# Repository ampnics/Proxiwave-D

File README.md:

# ProxiWave-D (PWD-v010A)
### Touchless Proximity-Based AC Relay Controller — Open Source Hardware by Ampnics

> An open-source, touchless proximity-based AC relay controller built on ATmega328-A with a VL53L0X Time-of-Flight sensor — designed for contactless switching of 220VAC loads by detecting hand proximity within 10–30mm range.

---

## 📸 Board Preview

| PCB Top View (Sensor Side) | PCB Bottom View (Power Side) |

---

---

## 📋 Table of Contents

- [Overview](#-overview)
- [Features](#-features)
- [How It Works](#-how-it-works)
- [Hardware Specifications](#-hardware-specifications)
- [GPIO Mapping](#-gpio-mapping)
- [Pin Description](#-pin-description)
- [Repository Structure](#-repository-structure)
- [Getting Started](#-getting-started)
- [Firmware Setup](#-firmware-setup)
- [Calibration](#-calibration)
- [Manufacturing](#-manufacturing)
- [Safety Warning](#️-safety-warning)
- [Contributing](#-contributing)
- [Support Us](#-support-us)
- [Connect With Us](#-connect-with-us)
- [License](#-license)

---

## 🔍 Overview

The **ProxiWave-D** is an open-source, touchless proximity relay controller designed for contactless switching of 220VAC loads. It uses a **VL53L0X Time-of-Flight (ToF) distance sensor** to detect hand proximity within a calibrated range of **10mm to 30mm**, triggering an onboard relay to switch AC loads — no physical contact required.

The board runs on **220VAC mains input**, converting it to **5V DC** via an onboard HLK-5M05 power supply module, and further to **3.3V** via an AMS1117-3.3 LDO — powering the ATmega328 and the VL53L0X sensor.

A **backup IR sensor connector (J3)** is also provided for redundancy or alternative sensing modes.

Designed in **KiCad 9.0.1** as part of the open-source hardware series by Ampnics.

---

## ✨ Features

- ✅ Touchless relay switching via VL53L0X ToF proximity sensor
- ✅ ATmega328-A microcontroller (8MHz crystal, 3.3V operation)
- ✅ 220VAC to 5VDC onboard power supply (HLK-5M05)
- ✅ 5V to 3.3V LDO regulator (AMS1117-3.3)
- ✅ SPDT relay for AC load switching
- ✅ MOV surge protection (10D561K)
- ✅ Fuse protection (0.5A / 250VAC)
- ✅ Backup IR sensor connector (J3)
- ✅ Buzzer feedback (MLT-8530)
- ✅ Power LED (Red) + Relay LED (Blue) + Status LED (Green)
- ✅ ICSP / SPI programming port (J2 — 2x3 header)
- ✅ Reset button (SW1)
- ✅ 5x screw terminal AC connector (J1)
- ✅ Test points — 5V, 3V3, GND, AVDD
- ✅ Fiducial markers + 4x mounting holes
- ✅ Sensing area clearly marked on PCB silkscreen
- ✅ Fully open-source — KiCad files included

---

## 🔄 How It Works

```
Hand approaches sensing area (10mm–30mm range)
              │
              ▼
   VL53L0X ToF Sensor detects distance
              │
              ▼
   ATmega328 reads I2C data from sensor
              │
              ▼
   Distance within calibrated threshold?
         ┌────┴────┐
        YES        NO
         │          │
         ▼          ▼
   Relay toggles  No action
   AC load ON/OFF
         │
         ▼
   Buzzer beeps + Status LED updates
```

---

## 🔧 Hardware Specifications

| Parameter | Details |
|---|---|
| Microcontroller | ATmega328-A |
| MCU Clock | 8MHz (External Crystal Y1) |
| MCU Operating Voltage | 3.3V |
| Proximity Sensor | VL53L0X ToF (I2C) |
| Sensor Operating Voltage | 2.6V – 3.6V (3.3V) |
| Detection Range | 10mm – 30mm (calibrated) |
| Input Voltage | 220V AC |
| Power Supply Module | HLK-5M05 (220VAC → 5VDC) |
| LDO Regulator | AMS1117-3.3 (5V → 3.3V) |
| Relay | G5LE-1 (SPDT) |
| Surge Protection | MOV 10D561K |
| Fuse | 0.5A / 250VAC |
| Buzzer | MLT-8530 |
| Status LEDs | Red (Power), Blue (Relay), Green (Status) |
| Programming | ICSP / SPI (J2 — 2x3 header) |
| Backup Sensor Port | J3 — 3-pin connector |
| PCB Tool | KiCad 9.0.1 |
| Board Revision | PWD-v010A |

---

## 📌 GPIO Mapping

| GPIO | Label | Function |
|---|---|---|
| PC1 / A1 | RIN / STS | Status indication |
| PC2 / A2 | RLY | Relay control |
| PC3 / A3 | BUZZER | Buzzer (MLT-8530) |
| PC4 / A4 | SDA | VL53L0X I2C SDA |
| PC5 / A5 | SCL | VL53L0X I2C SCL |
| PD2 / D2 | XSHUT | VL53L0X shutdown pin |
| PD4 / D4 | IR-BKP | Backup IR sensor (J3) |

---

## 🔌 Pin Description

### J1 — AC Screw Terminal (5-pin)

| Pin | Label | Description |
|---|---|---|
| 1 | AC/L | AC Line (Live) input |
| 2 | AC/N | AC Neutral input |
| 3 | NO | Relay Normally Open |
| 4 | C | Relay Common |
| 5 | NC | Relay Normally Closed |

### J2 — ICSP Programming Port (2x3)

| Pin | Label | Description |
|---|---|---|
| 1 | MISO | SPI MISO |
| 2 | VCC | 5V |
| 3 | SCK | SPI Clock |
| 4 | MOSI | SPI MOSI |
| 5 | RST | Reset |
| 6 | GND | Ground |

### J3 — Backup IR Sensor (3-pin)

| Pin | Label | Description |
|---|---|---|
| 1 | SIG | IR sensor signal |
| 2 | GND | Ground |
| 3 | 5V | Power |

### Signal Connector (3-pin)

| Pin | Label | Description |
|---|---|---|
| 1 | SIG | Signal output |
| 2 | GND | Ground |
| 3 | 3V3 | 3.3V output |

---

## 📁 Repository Structure

```
ProxiWave-D/
├── docs/                    # Datasheets and reference documents
├── imgs/                    # PCB renders and product images
├── manufacturing-files/     # Gerbers, BOM, CPL for fabrication
├── schematic/               # KiCad schematic & PCB files
├── ext-3d-models/           # External 3D models for KiCad
├── ext-lib/                 # External KiCad footprints & symbols
└── README.md
```

---

## 🚀 Getting Started

### Prerequisites
- [KiCad 9.0.1](https://www.kicad.org/) — to open schematic and PCB files
- [Arduino IDE](https://www.arduino.cc/en/software) — for firmware
- USBasp / AVRISP programmer — for flashing ATmega328
- [VL53L0X Arduino Library](https://github.com/pololu/vl53l0x-arduino)

### Clone the Repository
```bash
git clone https://github.com/ampnics/Proxiwave-D.git
cd Proxiwave-D
```

---

## 💻 Firmware Setup

### 1. Add ATmega328 (3.3V / 8MHz) Board Support

In Arduino IDE → **Preferences** → Additional Boards Manager URLs → add:
```
https://raw.githubusercontent.com/MCUdude/MiniCore/master/package_MCUdude_MiniCore_index.json
```
Then: **Tools → Board → Boards Manager → search "MiniCore" → Install**

Select these settings:
- Board: `ATmega328`
- Clock: `External 8MHz`
- Voltage: `3.3V`

### 2. Install Required Libraries
```
VL53L0X    → by Pololu
Wire       → built-in
```

### 3. Basic Firmware Structure

```cpp
#include <Wire.h>
#include <VL53L0X.h>

#define RELAY_PIN   A2   // PC2
#define BUZZER_PIN  A3   // PC3
#define XSHUT_PIN   2    // PD2
#define STATUS_PIN  A1   // PC1

#define MIN_RANGE   10   // mm
#define MAX_RANGE   30   // mm

VL53L0X sensor;

void setup() {
  pinMode(RELAY_PIN, OUTPUT);
  pinMode(BUZZER_PIN, OUTPUT);
  pinMode(XSHUT_PIN, OUTPUT);
  pinMode(STATUS_PIN, OUTPUT);

  digitalWrite(XSHUT_PIN, HIGH);
  Wire.begin();
  sensor.init();
  sensor.setTimeout(500);
  sensor.startContinuous();
}

void loop() {
  uint16_t distance = sensor.readRangeContinuousMillimeters();

  if (distance >= MIN_RANGE && distance <= MAX_RANGE) {
    digitalWrite(RELAY_PIN, !digitalRead(RELAY_PIN)); // Toggle relay
    digitalWrite(BUZZER_PIN, HIGH);
    delay(100);
    digitalWrite(BUZZER_PIN, LOW);
    delay(500); // Debounce delay
  }
}
```

### 4. Flash Using USBasp (ICSP)
```
Tools → Programmer → USBasp
Tools → Burn Bootloader (first time only)
Sketch → Upload Using Programmer
```

---

## 🎯 Calibration

> The VL53L0X sensor **must be calibrated** for reliable touchless operation.

- Default detection range: **10mm – 30mm**
- Adjust `MIN_RANGE` and `MAX_RANGE` in firmware based on your enclosure depth
- Mount sensor so the **sensing area circle** marked on PCB silkscreen is fully exposed
- Avoid reflective surfaces directly behind the sensing area
- Test under ambient light conditions before final deployment

---

## 🏭 Manufacturing

Fabrication files are available in `manufacturing-files/`:

- **Gerber files** — for PCB fabrication (JLCPCB / PCBWay)
- **BOM** — Bill of Materials with part numbers
- **CPL** — Component Placement List for SMT assembly

| Parameter | Value |
|---|---|
| Layers | 2 |
| Board Thickness | 1.6mm |
| Copper Weight | 1oz |
| Surface Finish | HASL / ENIG |
| Min Trace Width | 0.2mm |

---

## ⚠️ Safety Warning

> **This board operates at 220V AC mains voltage.**

- ⚠️ Do **NOT** touch the board while connected to mains power
- ⚠️ AC and DC sections are separated on the PCB — always respect this boundary
- ⚠️ Always use proper insulation and an enclosure before deployment
- ⚠️ Fuse (F1 — 0.5A/250VAC) must always be populated
- ⚠️ Intended for use by qualified engineers only

---

## 🤝 Contributing

Contributions are welcome from the community!

1. Fork the repository
2. Create your branch: `git checkout -b feature/your-feature`
3. Commit: `git commit -m "hw: your change"`
4. Push: `git push origin feature/your-feature`
5. Open a **Pull Request**

---

## ☕ Support Us

If this project helped you, consider buying us a coffee!

**[☕ Buy Me a Coffee — Support Ampnics](https://buymeacoffee.com/Ampnics)**

Your support helps us create more open-source hardware for the community!

---

## 🌐 Connect With Us

| Platform | Link |
|---|---|
| 📺 YouTube | [youtube.com/@ampnics](https://youtube.com/@ampnics?si=e0dvaRhfExjZXtJc) |
| 📸 Instagram | [instagram.com/ampnics](https://www.instagram.com/ampnics/) |
| 🐦 X (Twitter) | [twitter.com/ampnics](https://twitter.com/ampnics) |
| 💼 LinkedIn | [linkedin.com/company/ampnics](https://www.linkedin.com/company/ampnics/) |
| 🐙 GitHub | [github.com/ampnics](https://github.com/ampnics) |
| 💬 WhatsApp Community | [Join Here](https://chat.whatsapp.com/HgWOoxyOgLfGEkAPHPM01k) |
| 🌐 Website | [ampnics.com](https://ampnics.com) |

---

## 📄 License

This project is licensed under the **MIT License**.

You are free to use, modify, and distribute this design for personal and commercial purposes with attribution.

---

## 👨‍💻 Designed By

**Md Ammar Maniyar** — [Ampnics](https://github.com/ampnics)

*Engineered in India 🇮🇳*

---

⭐ **Star this repo** if it helped you — it motivates us to release more open-source hardware!

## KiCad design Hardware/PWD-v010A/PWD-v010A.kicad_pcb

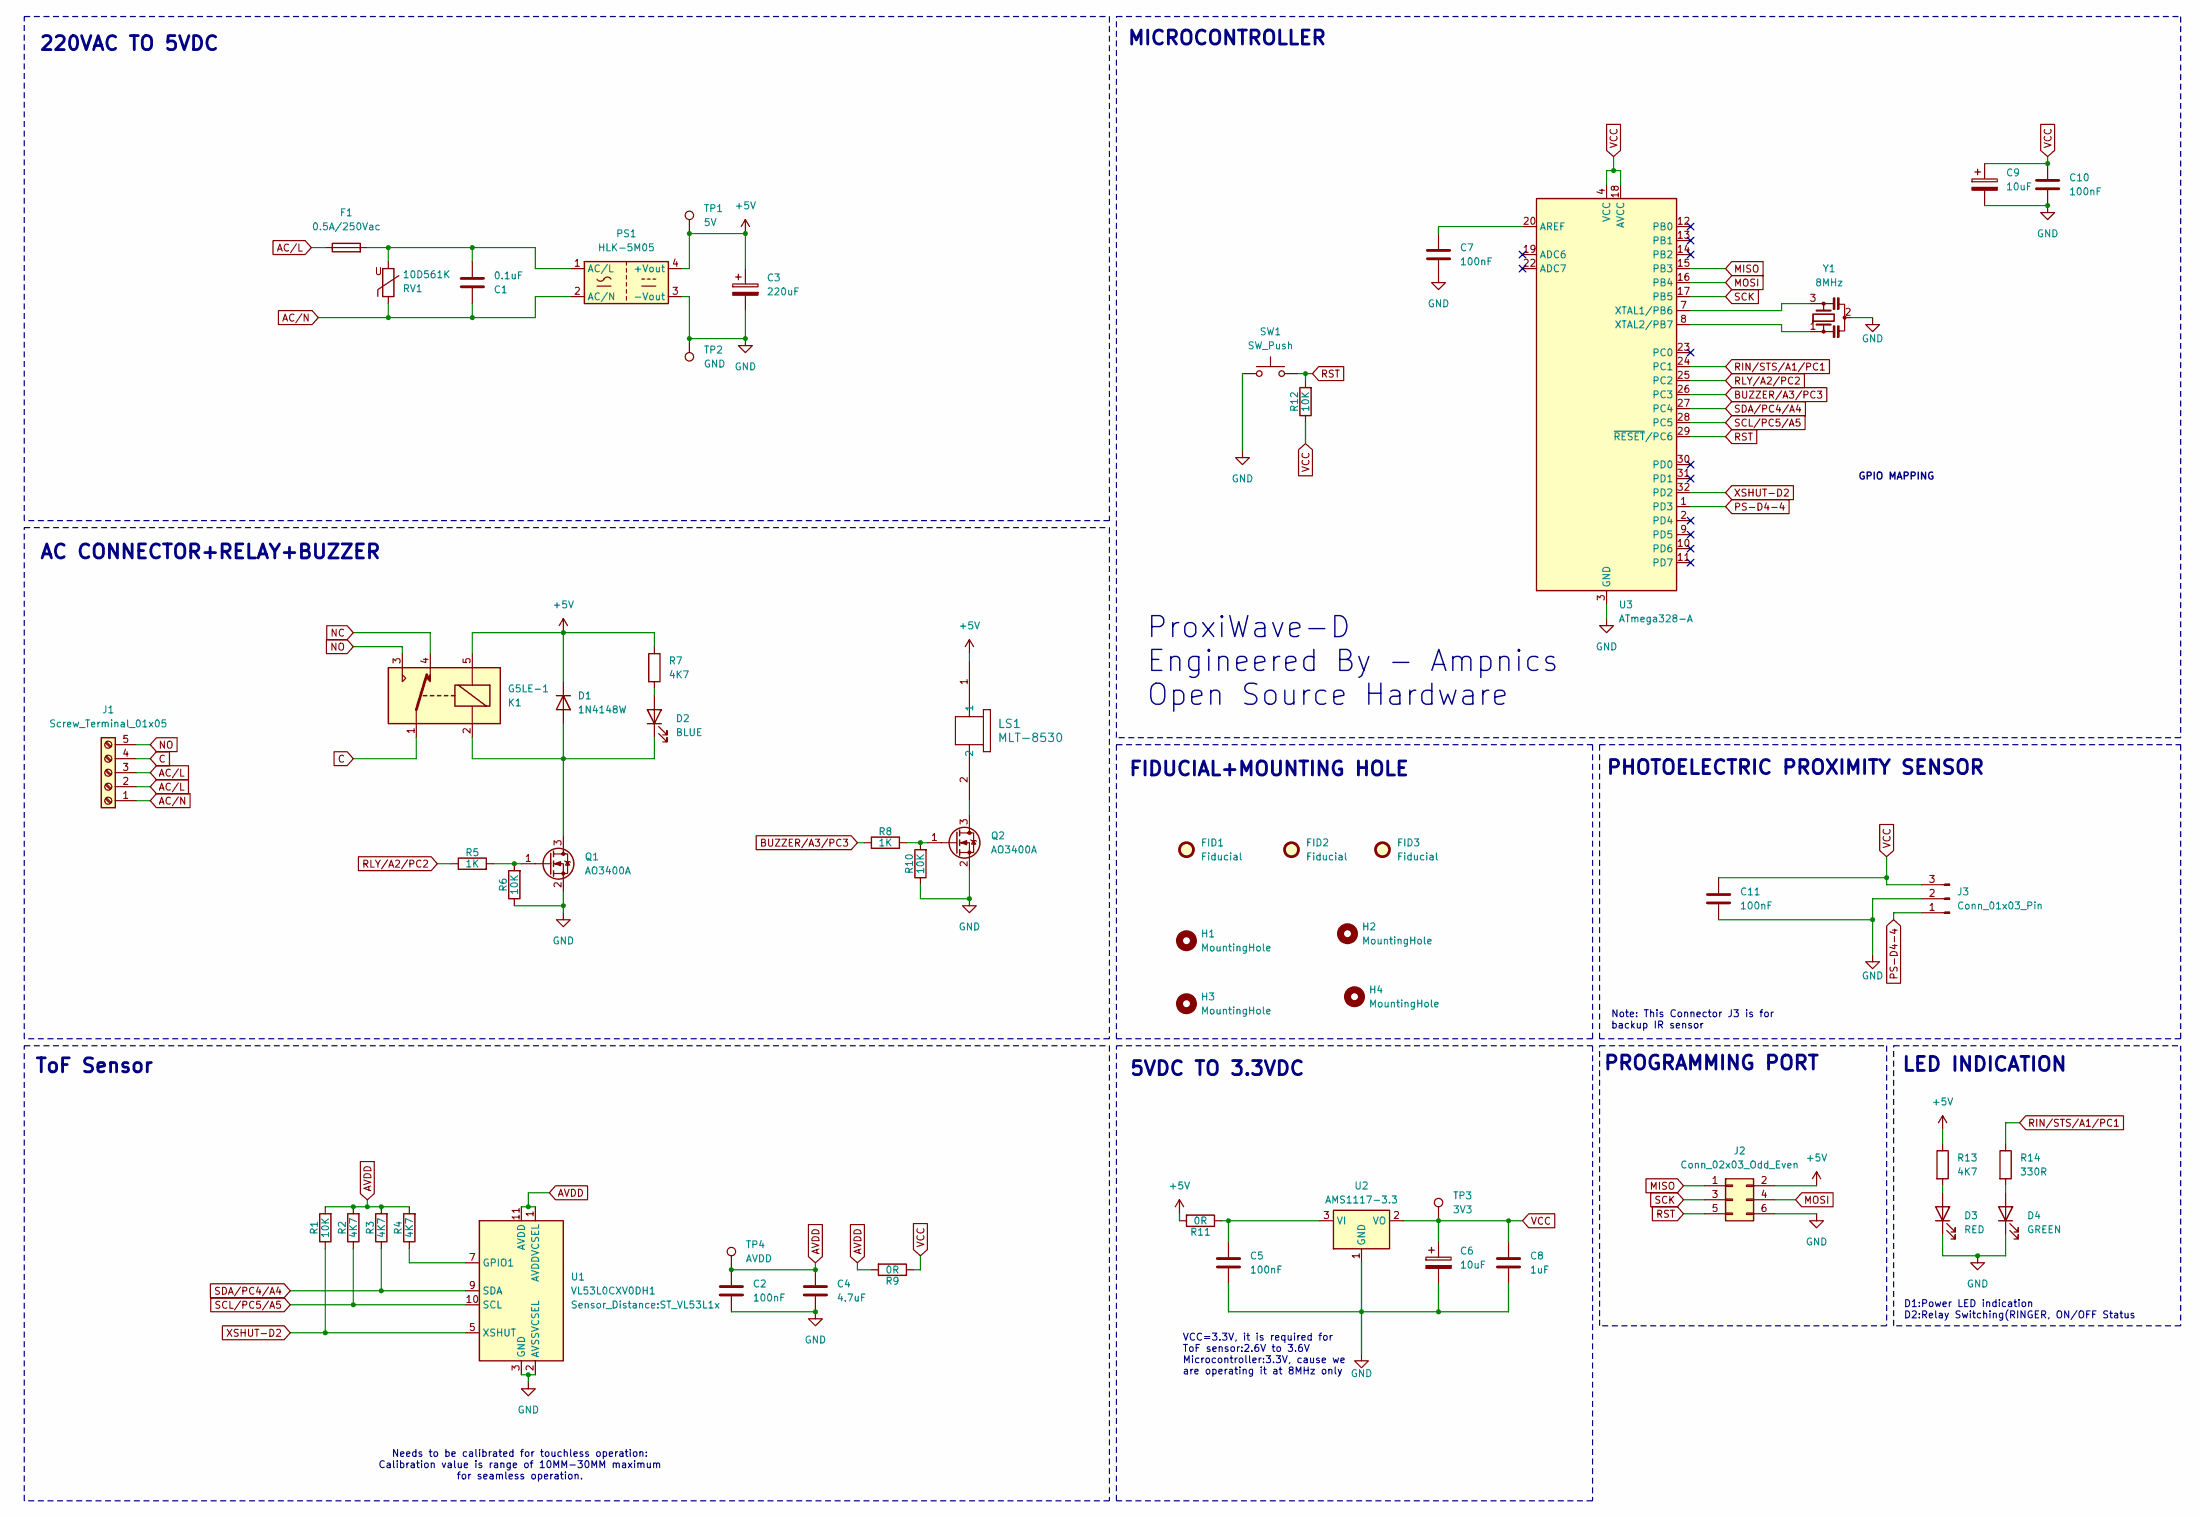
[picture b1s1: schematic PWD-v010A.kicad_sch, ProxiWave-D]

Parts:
C1: 0.1uF; C_Rect_L13.0mm_W6.0mm_P10.00mm_FKS3_FKP3_MKS4
C2, C5, C7, C10, C11: 100nF; C_0603_1608Metric
C3: 220uF; CP_Elec_8x10
C4: 4.7uF; C_0603_1608Metric
C6, C9: 10uF; CP_EIA-3216-18_Kemet-A
C8: 1uF; C_0603_1608Metric
D1: 1N4148W; D_SOD-123
D2: BLUE; LED_0603_1608Metric
D3: RED; LED_0603_1608Metric
D4: GREEN; LED_0603_1608Metric
F1: 0.5A/250Vac; Fuse_Littelfuse_395Series
FID1, FID2, FID3: Fiducial; Fiducial_0.75mm_Mask1.5mm
H1, H2, H3, H4: MountingHole; MountingHole_2.7mm
J1: Screw_Terminal_01x05; TerminalBlock_bornier-5_P5.08mm
J2: Conn_02x03_Odd_Even; PinHeader_2x03_P2.54mm_Vertical
J3: Conn_01x03_Pin; MPN B3B-XH-A
K1: G5LE-1; Relay_SPDT_Omron-G5LE-1
LS1: MLT-8530; MLT-8530_JHE
PS1: HLK-5M05; Converter_ACDC_Hi-Link_HLK-5Mxx
Q1, Q2: AO3400A; SOT-23
R1, R6, R10, R12: 10K; R_0603_1608Metric
R2, R3, R4, R7, R13: 4K7; R_0603_1608Metric
R5, R8: 1K; R_0603_1608Metric
R9, R11: 0R; R_0603_1608Metric
R14: 330R; R_0603_1608Metric
RV1: 10D561K; RV_Disc_D12mm_W5.8mm_P7.5mm
SW1: SW_Push; SW_Tactile_SKHH_Angled
TP1: 5V; TestPoint_Pad_D1.5mm
TP2: GND; TestPoint_Pad_D1.5mm
TP3: 3V3; TestPoint_Pad_D1.5mm
TP4: AVDD; TestPoint_Pad_D1.5mm
U1: VL53L0CXV0DH1; ST_VL53L1x
U2: AMS1117-3.3; SOT-223-3_TabPin2
U3: ATmega328-A; TQFP-32_7x7mm_P0.8mm
Y1: 8MHz; Resonator_SMD_Murata_CSTxExxV-3Pin_3.0x1.1mm

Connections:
+5V: C3.1, D1.1 (K), J2.2, K1.5, LS1.1, PS1.4 (+Vout), R7.1, R11.2, R13.1, TP1.1
AC/L: F1.1, J1.2, J1.3
AC/N: C1.1, J1.1, PS1.2 (AC/N), RV1.1
AVDD: C2.1, C4.1, R1.2, R2.2, R3.2, R4.2, R9.2, TP4.1, U1.1 (AVDDVCSEL), U1.11 (AVDD)
BUZZER/A3/PC3: R8.1, U3.26 (PC3)
C: J1.4, K1.1
GND: C2.2, C3.2, C4.2, C5.2, C6.2, C7.2, C8.2, C9.2, C10.2, C11.2, D3.1 (K), D4.1 (K), J2.6, J3.2, PS1.3 (-Vout), Q1.2 (S), Q2.2 (S), R6.1, R10.1, SW1.1, TP2.1, U1.2 (AVSSVCSEL), U1.3 (GND), U1.4 (GND), U1.6 (GND), U1.12 (GND), U2.1 (GND), U3.3 (GND), U3.5 (GND), U3.21 (GND), Y1.2
MISO: J2.1, U3.15 (PB3)
MOSI: J2.4, U3.16 (PB4)
NC: K1.4
NO: J1.5, K1.3
unnamed: D1.2 (A), D2.1 (K), K1.2, Q1.3 (D)
unnamed: D2.2 (A), R7.2
unnamed: D3.2 (A), R13.2
unnamed: D4.2 (A), R14.2
unnamed: C1.2, F1.2, PS1.1 (AC/L), RV1.2
unnamed: Q1.1 (G), R5.2, R6.2
unnamed: LS1.2, Q2.3 (D)
unnamed: Q2.1 (G), R8.2, R10.2
unnamed: R4.1, U1.7 (GPIO1)
unnamed: C5.1, R11.1, U2.3 (VI)
unnamed: C7.1, U3.20 (AREF)
unnamed: U3.7 (XTAL1/PB6), Y1.3
unnamed: U3.8 (XTAL2/PB7), Y1.1
PS-D4-4: J3.1, U3.1 (PD3)
RIN/STS/A1/PC1: R14.1, U3.24 (PC1)
RLY/A2/PC2: R5.1, U3.25 (PC2)
RST: J2.5, R12.2, SW1.2, U3.29 (~RESET/PC6)
SCK: J2.3, U3.17 (PB5)
SCL/PC5/A5: R2.1, U1.10 (SCL), U3.28 (PC5)
SDA/PC4/A4: R3.1, U1.9 (SDA), U3.27 (PC4)
VCC: C6.1, C8.1, C9.1, C10.1, C11.1, J3.3, R9.1, R12.1, TP3.1, U2.2 (VO), U3.4 (VCC), U3.6 (VCC), U3.18 (AVCC)
XSHUT-D2: R1.1, U1.5 (XSHUT), U3.32 (PD2)

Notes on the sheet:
VCC=3.3V, it is required for ToF sensor:2.6V to 3.6V Microcontroller:3.3V, cause we are operating it at 8MHz only
220VAC TO 5VDC
ToF Sensor
PHOTOELECTRIC PROXIMITY SENSOR
MICROCONTROLLER
ProxiWave-D Engineered By - Ampnics Open Source Hardware
5VDC TO 3.3VDC
Note: This Connector J3 is for backup IR sensor
GPIO MAPPING
PROGRAMMING PORT
AC CONNECTOR+RELAY+BUZZER
LED INDICATION
FIDUCIAL+MOUNTING HOLE
D1:Power LED indication D2:Relay Switching(RINGER, ON/OFF Status
Needs to be calibrated for touchless operation: Calibration value is range of 10MM-30MM maximum for seamless operation.

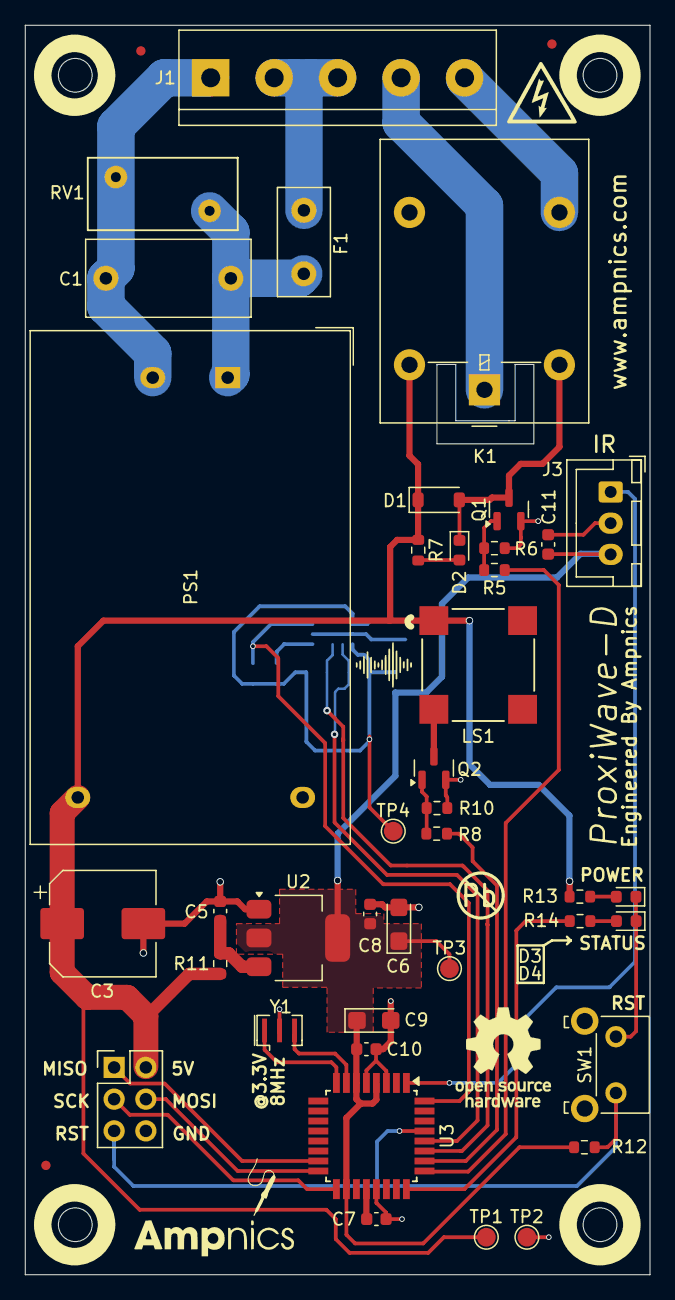
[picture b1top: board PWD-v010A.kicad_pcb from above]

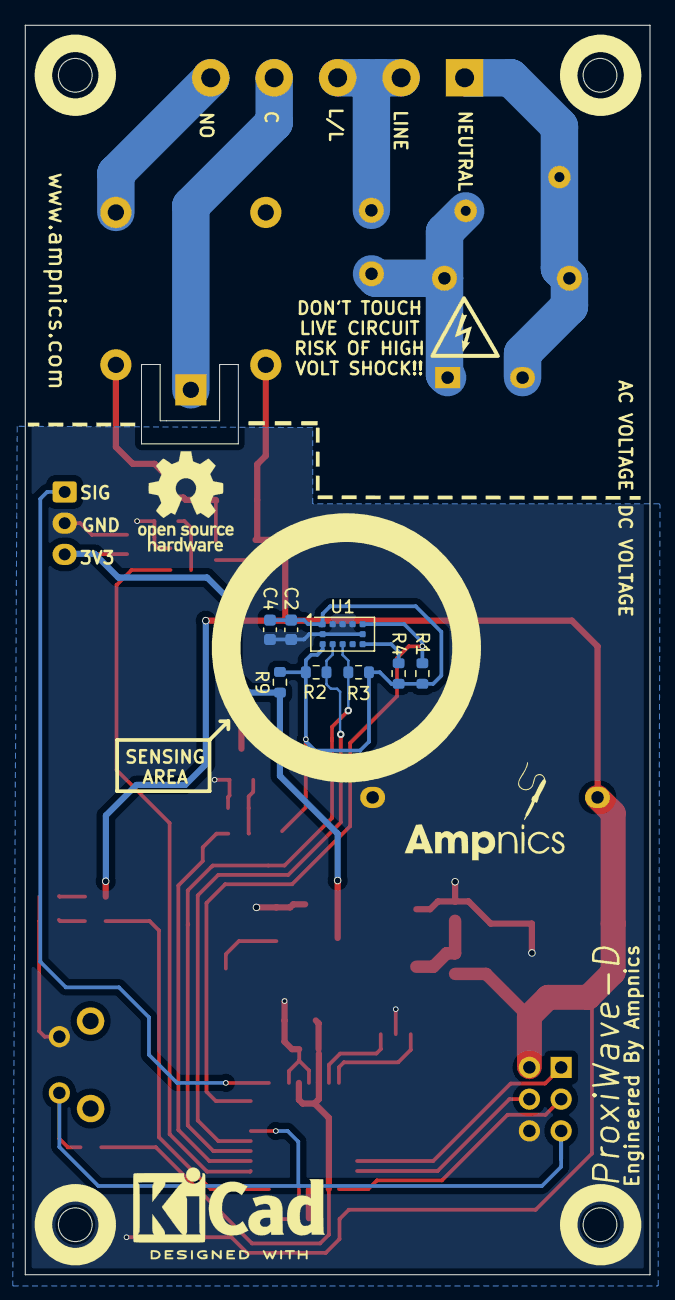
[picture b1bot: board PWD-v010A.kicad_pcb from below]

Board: 2 copper layers, 50.0 x 100.0 mm, 56 parts (8 on the bottom side), 32 nets.

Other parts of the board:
Sign-PbFree: LOGO_PBFREE

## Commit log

2026-04-19 Initial release: Proxiwave-D
2026-04-19 Create README.md for ProxiWave-D project
    Add detailed README for ProxiWave-D project with features, specifications, and setup instructions.

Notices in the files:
README.md:
License: MIT
